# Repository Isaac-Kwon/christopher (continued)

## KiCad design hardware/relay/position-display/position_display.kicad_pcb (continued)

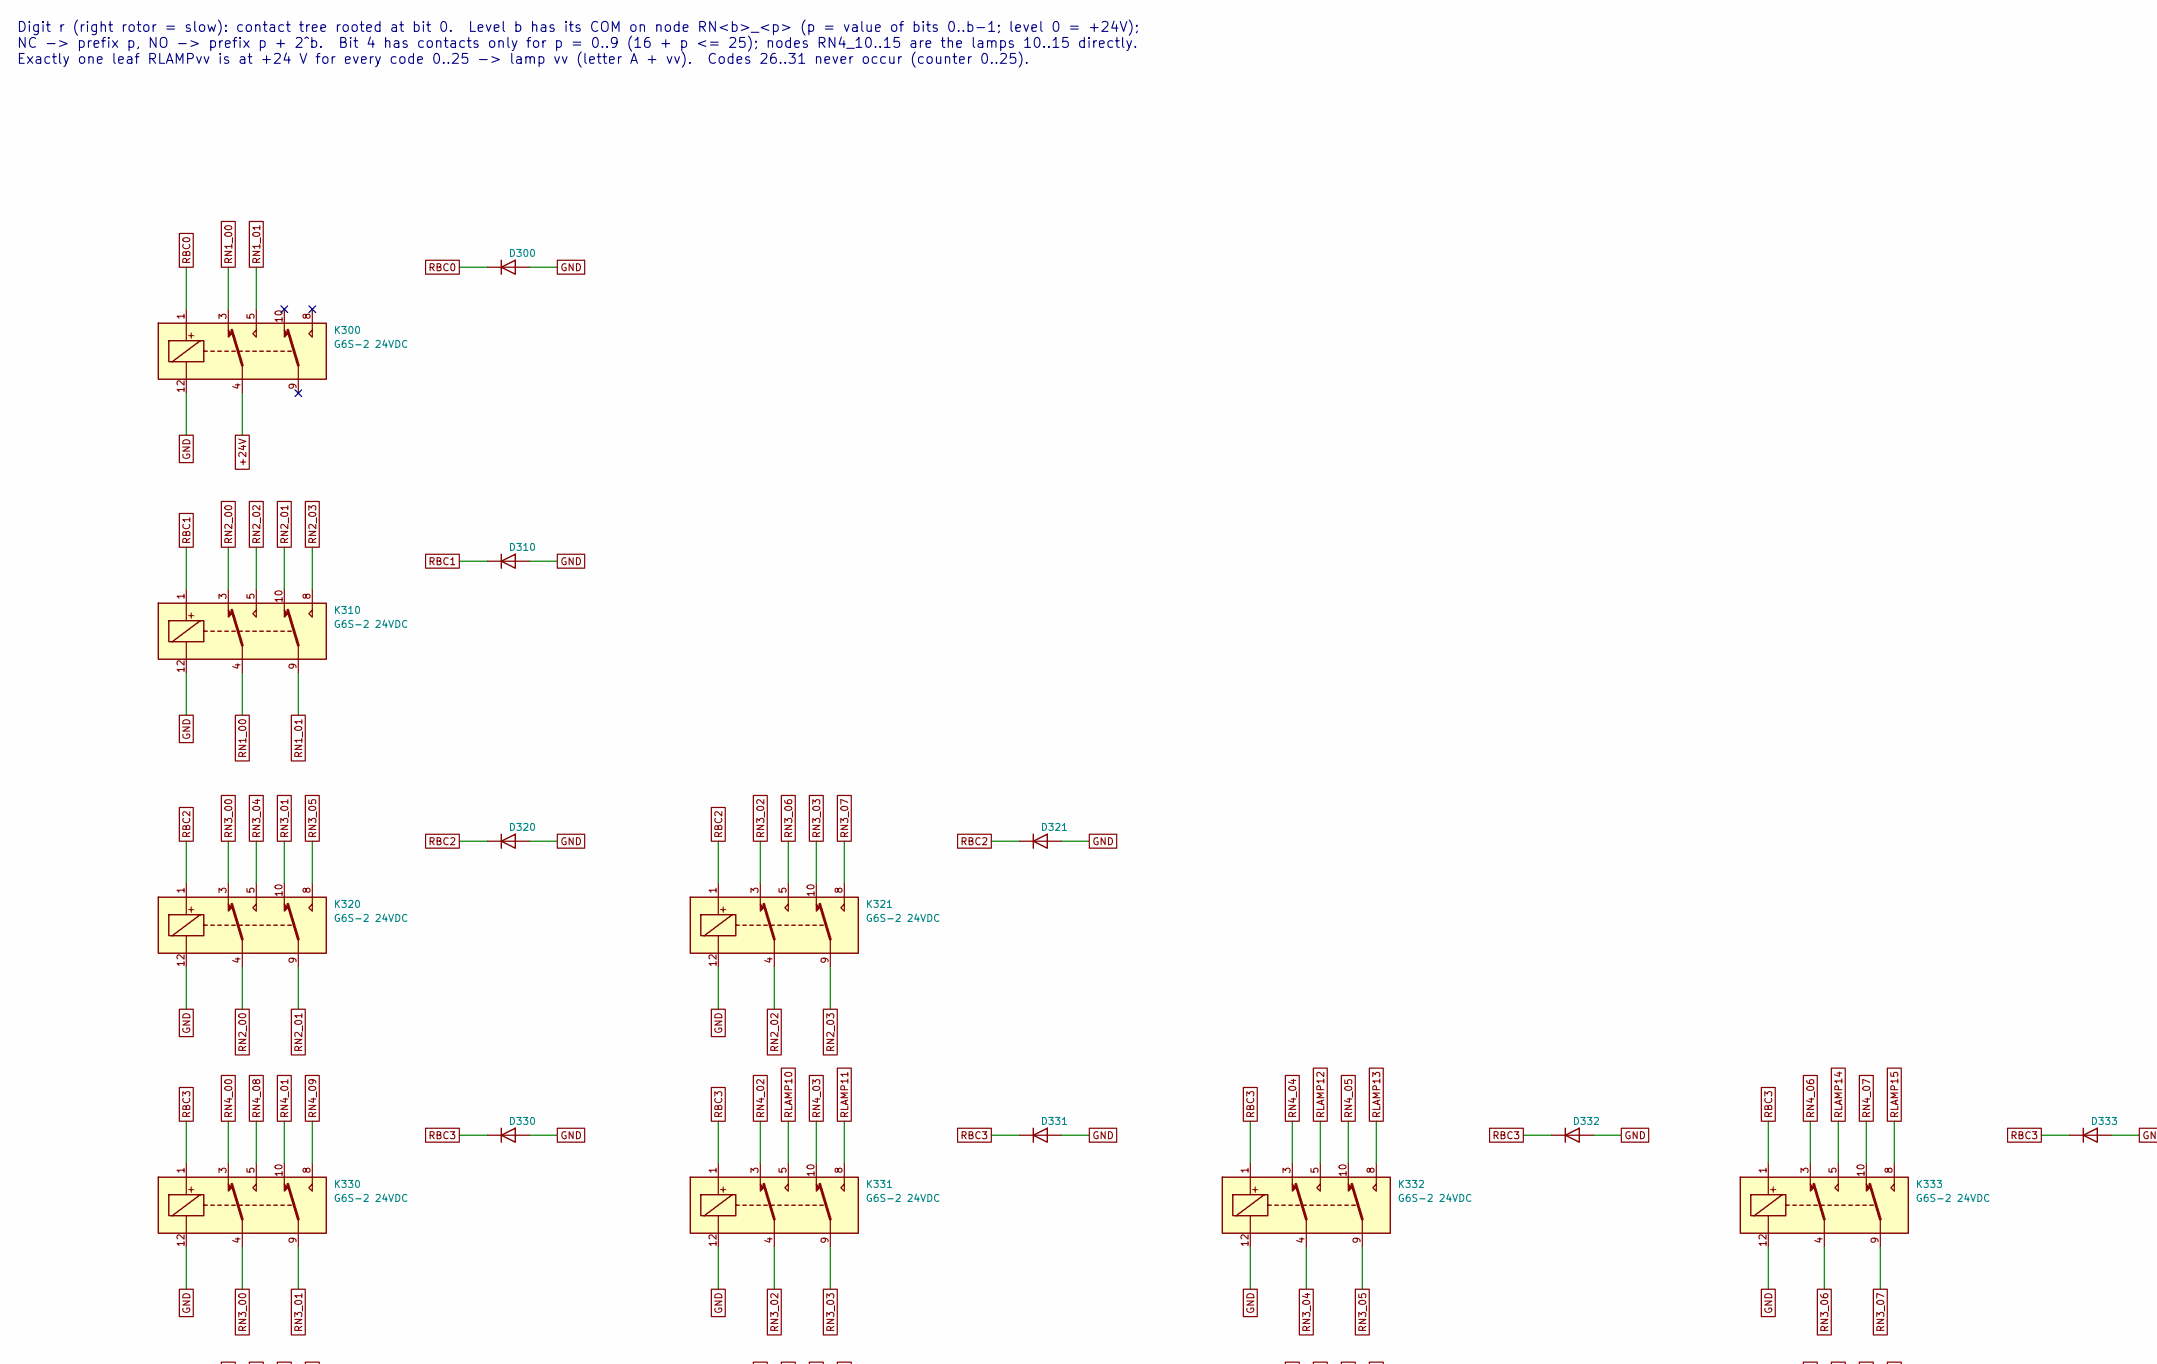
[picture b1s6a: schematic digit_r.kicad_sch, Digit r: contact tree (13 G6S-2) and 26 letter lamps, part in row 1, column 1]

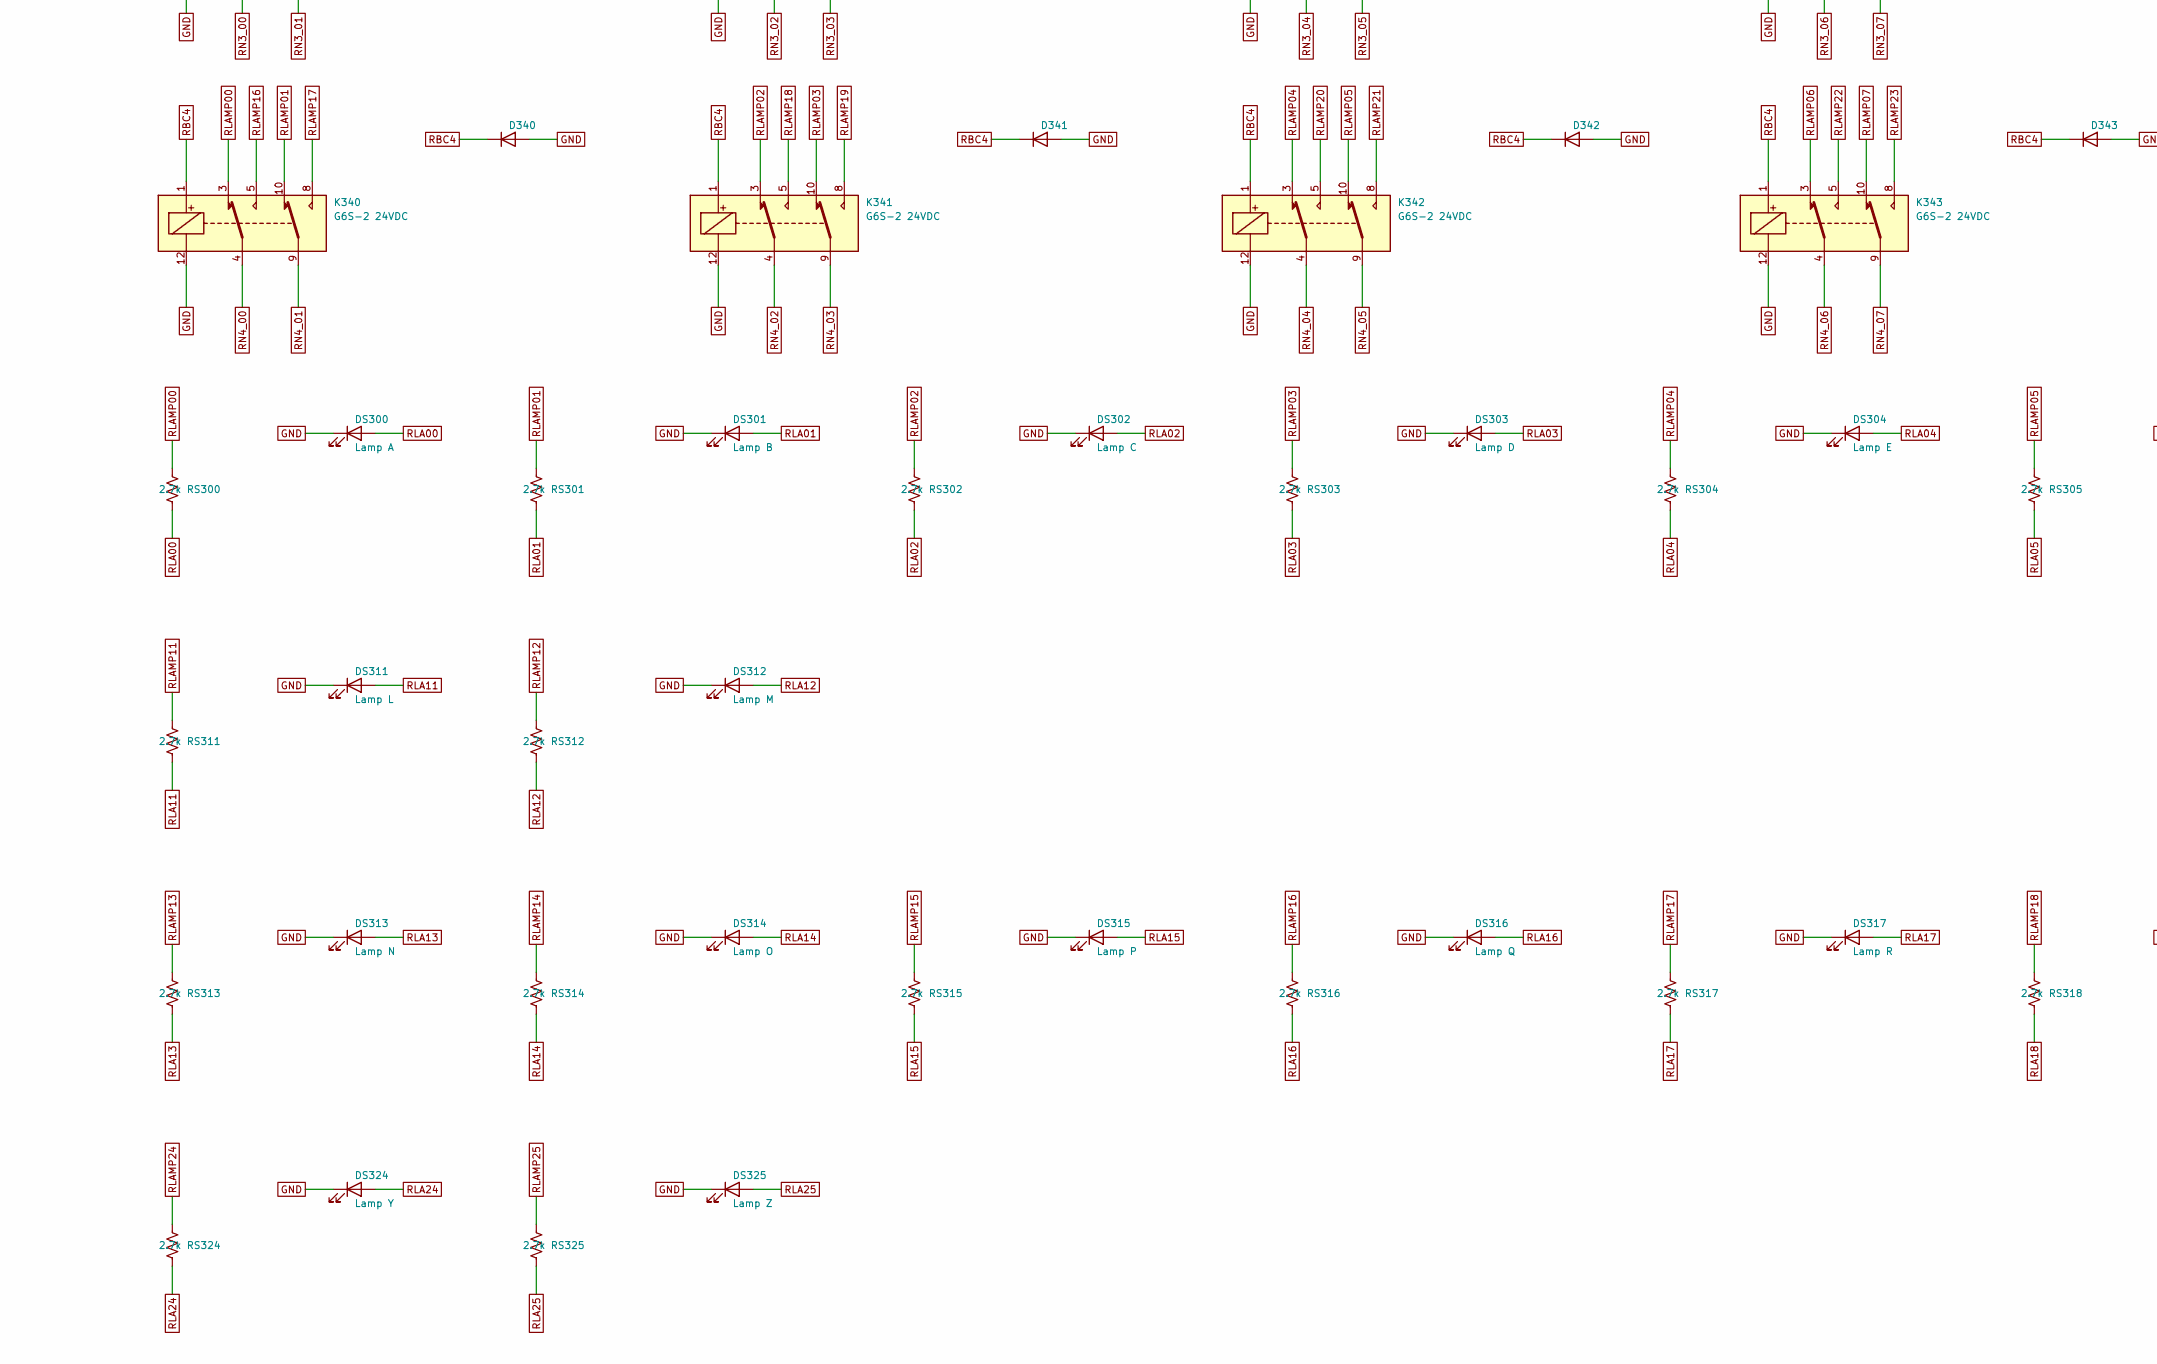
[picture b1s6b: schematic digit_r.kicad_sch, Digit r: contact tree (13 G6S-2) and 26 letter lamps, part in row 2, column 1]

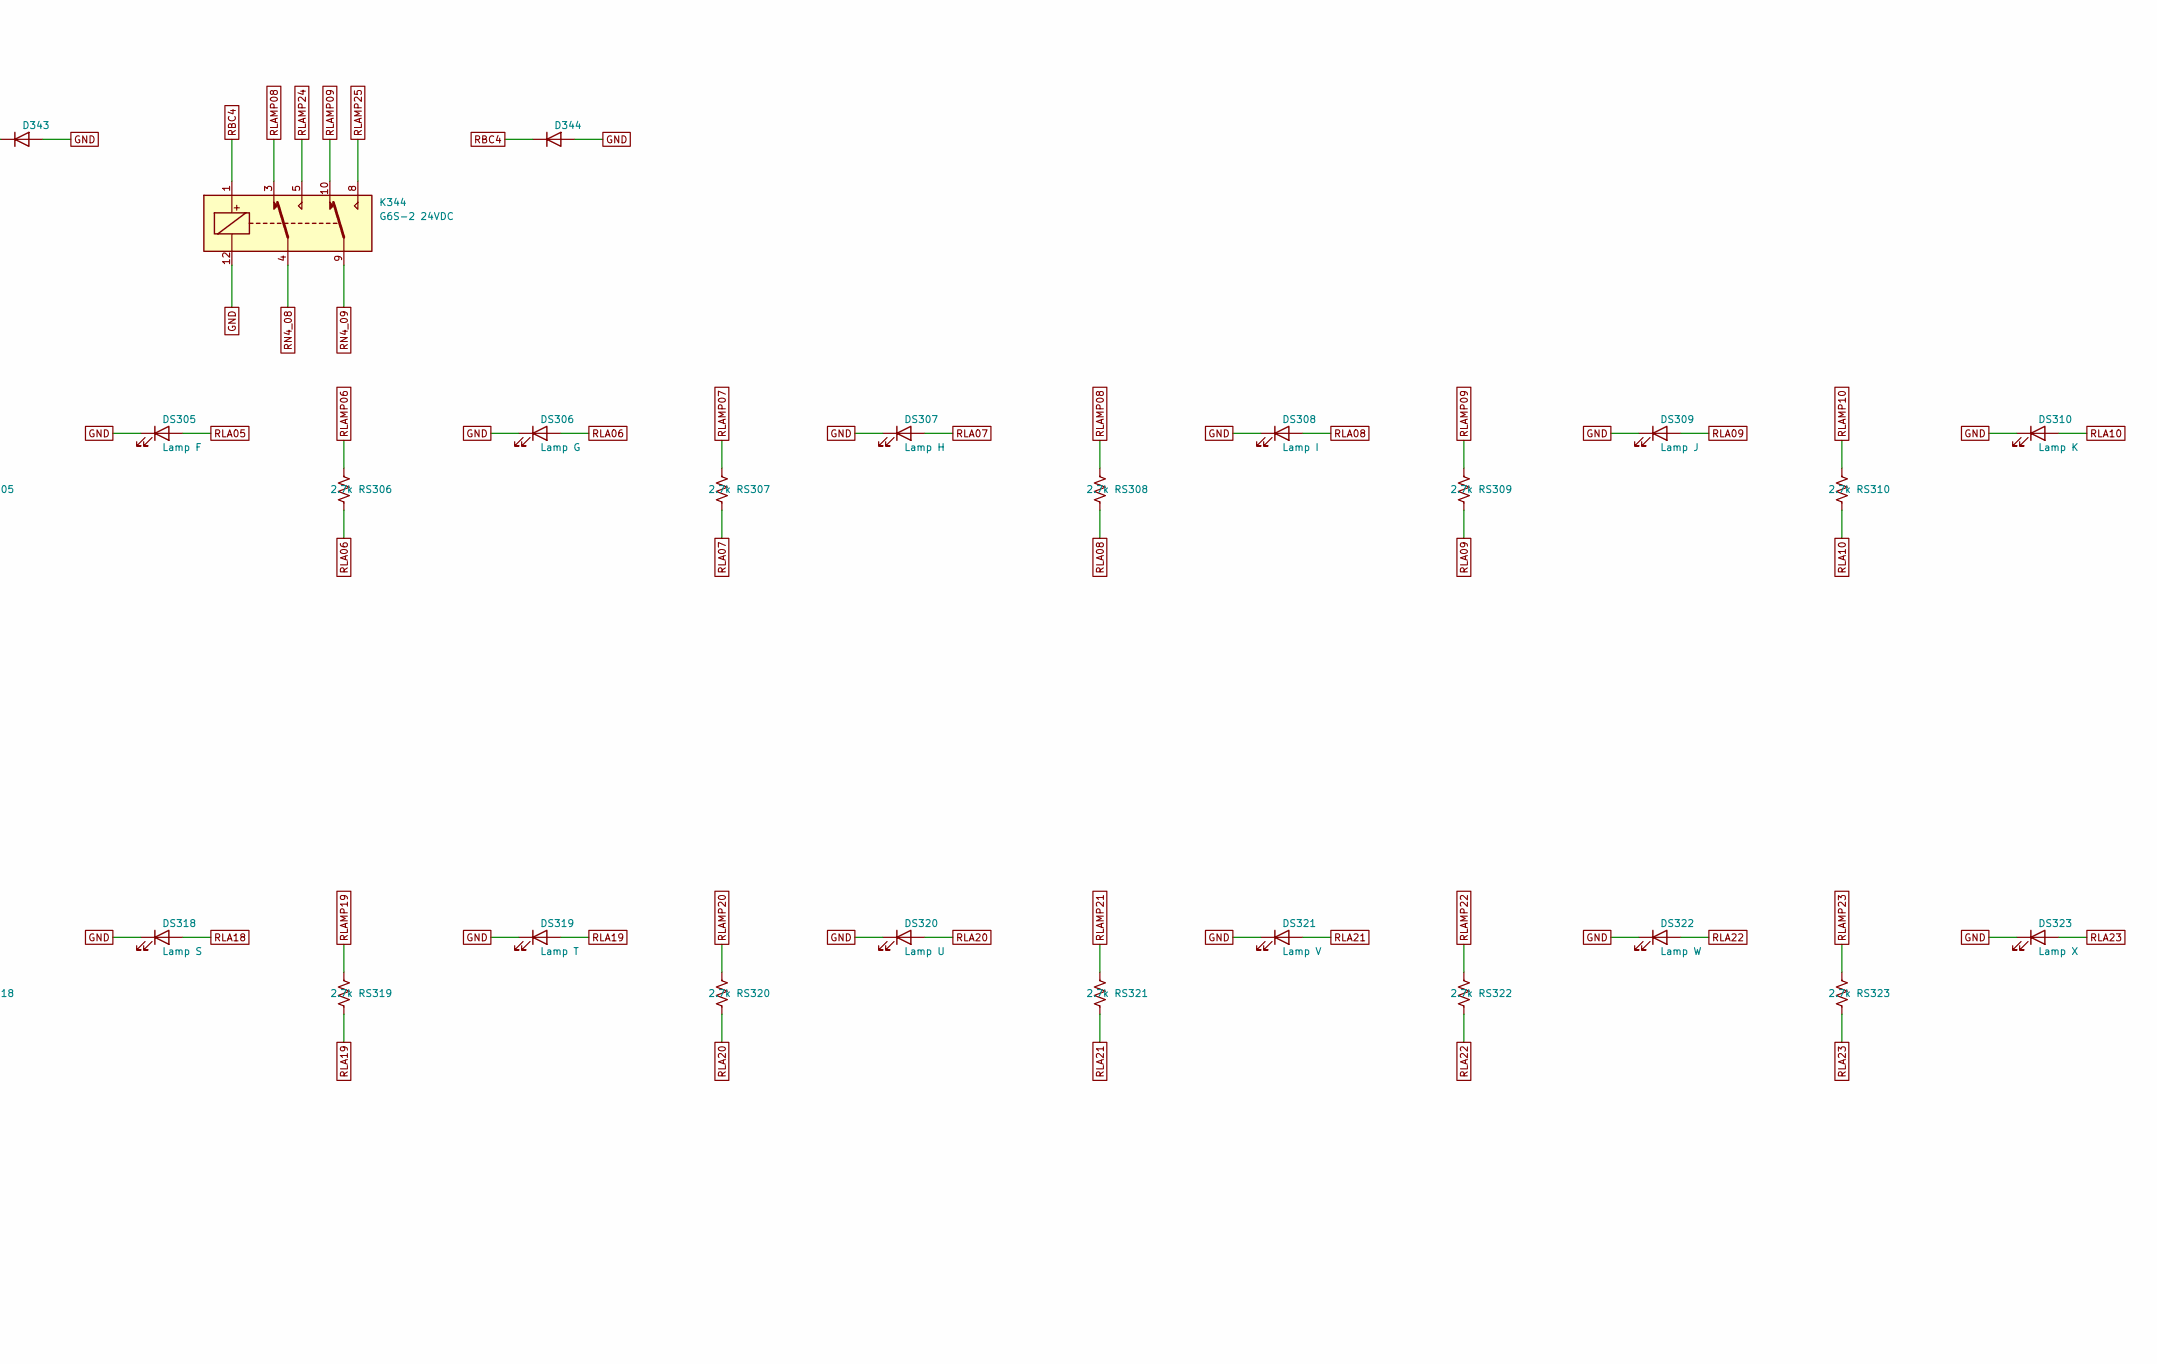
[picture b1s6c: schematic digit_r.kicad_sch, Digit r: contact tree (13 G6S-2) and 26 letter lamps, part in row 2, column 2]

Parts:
D300, D310, D320, D321, D330, D331, D332, D333, D340, D341, D342, D343, D344: 1N4148W; D_SOD-123
DS300: Lamp A; LED_D5.0mm
DS301: Lamp B; LED_D5.0mm
DS302: Lamp C; LED_D5.0mm
DS303: Lamp D; LED_D5.0mm
DS304: Lamp E; LED_D5.0mm
DS305: Lamp F; LED_D5.0mm
DS306: Lamp G; LED_D5.0mm
DS307: Lamp H; LED_D5.0mm
DS308: Lamp I; LED_D5.0mm
DS309: Lamp J; LED_D5.0mm
DS310: Lamp K; LED_D5.0mm
DS311: Lamp L; LED_D5.0mm
DS312: Lamp M; LED_D5.0mm
DS313: Lamp N; LED_D5.0mm
DS314: Lamp O; LED_D5.0mm
DS315: Lamp P; LED_D5.0mm
DS316: Lamp Q; LED_D5.0mm
DS317: Lamp R; LED_D5.0mm
DS318: Lamp S; LED_D5.0mm
DS319: Lamp T; LED_D5.0mm
DS320: Lamp U; LED_D5.0mm
DS321: Lamp V; LED_D5.0mm
DS322: Lamp W; LED_D5.0mm
DS323: Lamp X; LED_D5.0mm
DS324: Lamp Y; LED_D5.0mm
DS325: Lamp Z; LED_D5.0mm
K300, K310, K320, K321, K330, K331, K332, K333, K340, K341, K342, K343, K344: G6S-2 24VDC; Relay_DPDT_Omron_G6S-2
RS300, RS301, RS302, RS303, RS304, RS305, RS306, RS307, RS308, RS309, RS310, RS311, RS312, RS313, RS314, RS315, RS316, RS317, RS318, RS319, RS320, RS321, RS322, RS323, RS324, RS325: 2.7k; R_1206_3216Metric

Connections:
+24V: K300.4; also elsewhere on the board
GND: D300.2 (A), D310.2 (A), D320.2 (A), D321.2 (A), D330.2 (A), D331.2 (A), D332.2 (A), D333.2 (A), D340.2 (A), D341.2 (A), D342.2 (A), D343.2 (A), D344.2 (A), DS300.1 (K), DS301.1 (K), DS302.1 (K), DS303.1 (K), DS304.1 (K), DS305.1 (K), DS306.1 (K), DS307.1 (K), DS308.1 (K), DS309.1 (K), DS310.1 (K), DS311.1 (K), DS312.1 (K), DS313.1 (K), DS314.1 (K), DS315.1 (K), DS316.1 (K), DS317.1 (K), DS318.1 (K), DS319.1 (K), DS320.1 (K), DS321.1 (K), DS322.1 (K), DS323.1 (K), DS324.1 (K), DS325.1 (K), K300.12, K310.12, K320.12, K321.12, K330.12, K331.12, K332.12, K333.12, K340.12, K341.12, K342.12, K343.12, K344.12; also elsewhere on the board
RBC0: D300.1 (K), K300.1; also elsewhere on the board
RBC1: D310.1 (K), K310.1; also elsewhere on the board
RBC2: D320.1 (K), D321.1 (K), K320.1, K321.1; also elsewhere on the board
RBC3: D330.1 (K), D331.1 (K), D332.1 (K), D333.1 (K), K330.1, K331.1, K332.1, K333.1; also elsewhere on the board
RBC4: D340.1 (K), D341.1 (K), D342.1 (K), D343.1 (K), D344.1 (K), K340.1, K341.1, K342.1, K343.1, K344.1; also elsewhere on the board
RLA00: DS300.2 (A), RS300.2
RLA01: DS301.2 (A), RS301.2
RLA02: DS302.2 (A), RS302.2
RLA03: DS303.2 (A), RS303.2
RLA04: DS304.2 (A), RS304.2
RLA05: DS305.2 (A), RS305.2
RLA06: DS306.2 (A), RS306.2
RLA07: DS307.2 (A), RS307.2
RLA08: DS308.2 (A), RS308.2
RLA09: DS309.2 (A), RS309.2
RLA10: DS310.2 (A), RS310.2
RLA11: DS311.2 (A), RS311.2
RLA12: DS312.2 (A), RS312.2
RLA13: DS313.2 (A), RS313.2
RLA14: DS314.2 (A), RS314.2
RLA15: DS315.2 (A), RS315.2
RLA16: DS316.2 (A), RS316.2
RLA17: DS317.2 (A), RS317.2
RLA18: DS318.2 (A), RS318.2
RLA19: DS319.2 (A), RS319.2
RLA20: DS320.2 (A), RS320.2
RLA21: DS321.2 (A), RS321.2
RLA22: DS322.2 (A), RS322.2
RLA23: DS323.2 (A), RS323.2
RLA24: DS324.2 (A), RS324.2
RLA25: DS325.2 (A), RS325.2
RLAMP00: K340.3, RS300.1
RLAMP01: K340.10, RS301.1
RLAMP02: K341.3, RS302.1
RLAMP03: K341.10, RS303.1
RLAMP04: K342.3, RS304.1
RLAMP05: K342.10, RS305.1
RLAMP06: K343.3, RS306.1
RLAMP07: K343.10, RS307.1
RLAMP08: K344.3, RS308.1
RLAMP09: K344.10, RS309.1
RLAMP10: K331.5, RS310.1
RLAMP11: K331.8, RS311.1
RLAMP12: K332.5, RS312.1
RLAMP13: K332.8, RS313.1
RLAMP14: K333.5, RS314.1
RLAMP15: K333.8, RS315.1
RLAMP16: K340.5, RS316.1
RLAMP17: K340.8, RS317.1
RLAMP18: K341.5, RS318.1
RLAMP19: K341.8, RS319.1
RLAMP20: K342.5, RS320.1
RLAMP21: K342.8, RS321.1
RLAMP22: K343.5, RS322.1
RLAMP23: K343.8, RS323.1
RLAMP24: K344.5, RS324.1
RLAMP25: K344.8, RS325.1
RN1_00: K300.3, K310.4
RN1_01: K300.5, K310.9
RN2_00: K310.3, K320.4
RN2_01: K310.10, K320.9
RN2_02: K310.5, K321.4
RN2_03: K310.8, K321.9
RN3_00: K320.3, K330.4
RN3_01: K320.10, K330.9
RN3_02: K321.3, K331.4
RN3_03: K321.10, K331.9
RN3_04: K320.5, K332.4
RN3_05: K320.8, K332.9
RN3_06: K321.5, K333.4
RN3_07: K321.8, K333.9
RN4_00: K330.3, K340.4
RN4_01: K330.10, K340.9
RN4_02: K331.3, K341.4
RN4_03: K331.10, K341.9
RN4_04: K332.3, K342.4
RN4_05: K332.10, K342.9
RN4_06: K333.3, K343.4
RN4_07: K333.10, K343.9
RN4_08: K330.5, K344.4
RN4_09: K330.8, K344.9

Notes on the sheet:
Digit r (right rotor = slow): contact tree rooted at bit 0. Level b has its COM on node RN<b>_<p> (p = value of bits 0..b-1; level 0 = +24V); NC -> prefix p, NO -> prefix p + 2^b. Bit 4 has contacts only for p = 0..9 (16 + p <= 25); nodes RN4_10..15 are the lamps 10..15 directly. Exactly one leaf R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

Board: 4 copper layers, 398 parts (0 on the bottom side), 324 nets, no tracks yet.

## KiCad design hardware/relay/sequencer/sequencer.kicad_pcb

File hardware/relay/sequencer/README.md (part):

# 릴레이식 클럭 순서기 보드 (Phase 3 R 트랙, 회로도 + 기판 배치)

작성일: 2026-11-15 · 상태: **회로도(KiCad 10) 생성·ERC 0건, 넷리스트 스위치 수준 시뮬레이션과 음성 시험 완료, 기판 배치(미배선) 생성·검증 완료, 배선은 사용자가.** 같은 날 `HOME` 끝의 `CLEAR`(0003 4.4절 (나))를 더함. 2026-11-16 다이얼 띠의 **속도 선택(관찰 모드)과 한 걸음 버튼** 입력 J10 `PANEL`을 더함(2.1·3.3절) · 관련: `hardware/relay/offset-dial/README.md` 5절(다이얼 띠 조작 장치), `docs/decisions/0003-interfaces.md`(L1–L9, 4절, 5.2절 제어 커넥터, 8.4절 K7), `docs/decisions/0001-test-register-timing.md`, `hardware/relay/counter-board/README.md`(2.5절 CK/NCK·HOME, 4절 타이밍, 8절), `hardware/relay/concept.md` 6절, `hardware/relay/layout.md` 3.5·3.7절(자리 250 × 228 × 40, 대기), `hardware/common/power-unit.md`(F38, `+24V_SW`)

**표기.** **(계산)** = 이 문서의 산술, **(추정)** = 실측 전 값, **(미확인)** = 데이터시트로 확인하지 못한 것.

## 1. 무엇인가

릴레이식 뱅크의 **위치 순서기**다. 한 위치마다 `CK`/`NCK`(두 상, 단일 전환 접점), `STROBE`·`JUDGE`·`CLEAR`를 0003 L1–L9의 폭과 간격으로 내고, `RUN`·`STOP_LATCH`·`HOME`을 받아 정지·재출발·`HOME`(프리셋)·`END`·대기를 처리한다. 다이얼 띠의 **속도 선택**(빠름 63 ms / 관찰 270 ms)과 **한 걸음 버튼**(누를 때마다 위치 주기 하나)을 J10으로 받는다. 계수기 공통 보드의 `POS`(l, m, r)를 제어 커넥터 7–21번으로 중계하고, 안전 고리(`ESTOP`, `ILOCK`)의 뱅크 쪽 자리를 준다.

| 항목 | 값 |
|---|---|
| 릴레이 | **G6S-2 50개**(기능 릴레이 33 + 접점을 늘리는 쌍둥이 17). 그 가운데 6개(`KOBS`, `KSP`, `KSA`(+b), `KSC`(+b))가 속도 선택·한 걸음 |
| 능동 부품 | LMC555 1, 74HC4017 1, TBD62783A 2, TSR 1-2450(5 V) 1 |
| 다이오드류 | 다이오드 72, 쇼트키 8, 제너 16(+ 게이트 제너 1), TVS 1, P채널 MOSFET 1 |
| 그 밖 | 자동 복귀 퓨즈 27, 저항 65, 커패시터 12, LED 33, 트리머 1, 납땜 점퍼 3 |
| 커넥터 | D-sub 37 수 1(제어), D-sub 25 수 2(`POS` 입력, `UNIT_BUS` 탭), D-sub 9 수 2(`CLOCK` A/B), 나사 단자 4극 3 + 2극 2 |
| 부품 합계 | 309개(장착 구멍 4 포함) |
| 기판 | 250 × 228 mm 4층(시프터·계수기와 같은 카드 규격), 높이 40 mm 이내 **(계산)**: 가장 높은 부품 100 µF 전해 12 mm, 릴레이 10 mm |

### 1.1 원리: 릴레이가 정한다, 시간 기준만 전자식

설계 원칙("릴레이가 판정한다, 전자 장치는 시간만 알린다")에 맞춰 **순서·조건·잠금은 전부 릴레이 접점**이다: 위치 한 주기의 단계 선택, `RUN`을 본 뒤의 `CK` 결정(`KCKH`), 정지 뒤의 "나아가기 먼저"(`KADV`), `HOME` 순서(`KHL`), 프리셋 중의 `LOAD`·`NCK` 겹침, `END` 판정(`KR25`·`KEND`), 대기(`KSB`), 비상 정지 때의 전부 놓기. 모든 출력은 릴레이 접점이 +24 V를 잇는 방식이다.

**전자식인 것은 시간 기준 하나**다: LMC555(발진기) + 74HC4017(링 계수기), 곧 "6.3 ms마다 다음 단계"라는 박자다. 이것은 기어식에서 광센서와 슬롯 원판이 하는 일("언제")과 같고, 정지·진행 여부는 결정하지 않는다. 릴레이 시간 기준을 쓰지 않은 이유(요약):

1. 0003의 폭·간격은 모두 하한이다. 하한을 **보증**하려면 타이밍 편차가 릴레이 동작 편차(2.5–5 ms)보다 작아야 한다. RC로 지연시키는 릴레이는 동작 전압이 정격의 일정 비율 **이상**이라는 값(최대 80% **(미확인)**)만 알려져 있어 지연의 하한을 보증할 수 없다(동작 전압 50–80%면 같은 RC의 지연이 2배 이상 흩어진다 (계산)).
2. 릴레이 사슬로 박자를 만들면 단계마다 편차가 쌓여(릴레이 하나 최대 ±1.25 ms 편차, 사슬 길이만큼) 위치 주기가 70–80 ms가 된다.
3. 전자식 클럭을 기본으로 하고 릴레이 발진기는 전시 요소로 선택할 수 있게 한다는 `concept.md` 6절의 방침과 같다. 발진기를 릴레이로 바꿀 자리는 U1 하나다(10 kΩ·22 nF의 RC가 박자를 정한다).

**속도 선택도 박자만 바꾼다.** 관찰 모드는 555의 R2에 680 kΩ을 직렬로 넣어(평소에는 릴레이 접점 두 개가 이 저항을 단락한다) 틱을 27 ms로 늘린다(2.1절). 어느 단계가 언제 나오는지, 주기를 시작·완료하는지는 그대로 릴레이 접점이 정한다. 한 걸음 버튼도 마찬가지로 "주기 하나를 시작해도 된다"를 릴레이 래치로 만들 뿐이다(3.3절).

링 계수기의 출력은 **창**(다이오드 OR)이 되어 TBD62783A(24 V 고측 구동기)의 입력이 되고, 그 출력이 출력 릴레이의 코일을 먹인다. 창과 구동기 사이에는 릴레이 접점이 직렬로 들어간다(`KENW`, `KENK`, `KCKH`, `KHL` …): 접점이 닫혀 있어야만 창이 코일에 닿는다.

## 2. 위치 한 주기의 시각표

링 상태 Q0–Q9(한 틱 T = 6.3 ms, 한 주기 10틱 = **63 ms**, 트리머로 T 4.7–7.8 ms)와 릴레이 출력 **(커넥터 면, 계산: 시뮬레이션이 확인)**:

| 링 상태 | 창 | 구동되는 릴레이 | 하는 일 |
|---|---|---|---|
| Q0–Q1 | WS | `KS` (게이트 `KENW`) | `STROBE` |
| Q3–Q4 | WJ | `KJ` (게이트 `KENW`) | `JUDGE` |
| Q6 | — | `KCKH` 표본(`RUN`이 높을 때, 또는 한 걸음 주기에 `STOP_LATCH`가 낮을 때) | `CK`를 낼지 결정, 닫히면 Q6–Q8(WC)로 스스로 유지 |
| Q6–Q8 | WC | `KC` (게이트 `KENK`) | `CLEAR` |
| Q7–Q8 | WK | `KCKA`·`KCKB` (게이트 `KENK`, `KCKH`) | `CK` (결정 `KCKH`가 닫혔으면) 또는 나아가기 보류 `KADV` 세트(열렸으면) |
| Q9 | — | `KST`(주차) | 링이 선다(`KGO`가 없을 때), `STOPPED` |

| 규칙 (0003 3.3절) | 요구 | 시뮬레이션 최소값(릴레이 시간 최악·최선·무작위, 링 ±3%; 속도 전환·한 걸음 시나리오 포함) | 여유 |
|---|---|---|---|
| L1 `STROBE` 폭 | ≥ 7.5 ms | 8.23 | 0.73 |
| L2 `JUDGE` 오름 − `STROBE` 오름 | ≥ 11.5 | 15.66 | 4.2 |
| L3 `JUDGE` 폭 | ≥ 7.5 | 8.23 | 0.73 |
| L4 `CLEAR` 오름 − `JUDGE` 내림 | ≥ 1.5 | 4.86 | 3.4 |
| L5 `CLEAR` 폭 | ≥ 12.5 | 14.40 | 1.9 |
| L6 다음 `STROBE` 오름 − `CLEAR` 내림 | ≥ 1.5 | 4.85 | 3.4 |
| L9 `CK` 오름 → 다음 `STROBE` 오름(시프터 안정 13) | ≥ 13 | 15.69 | 2.7 |
| `CK` 폭(계수기가 요구하는 5 ms) | ≥ 5 | 8.23 | 3.2 |
| `HOME` 끝의 `CLEAR` 폭 (L5, 3.2절) | ≥ 12.5 | 14.54 | 2.0 |
| 첫 `STROBE` 오름 − `HOME` 끝 `CLEAR` 내림 (L6, `HOME` 중에 시작 스위치를 켠 경우) | ≥ 1.5 | 20.68 | 19 |

- **주기는 63 ms, 초당 15.9 위치**(전체 17,576 위치 약 18.5분, 90번 정지를 넣은 전체 시뮬레이션은 18.8분)다. `concept.md` 6절의 35 ms(10.3분)는 **출력 쪽 타이밍 편차가 0일 때** 성립하는 값이다. 릴레이 접점이 출력이면 `STROBE` 폭만 해도 구동 폭 + (복귀 − 동작) = 구동 폭 − 3.5…4.1 ms로 줄어(동작 2.5–5, 복귀 1.5–4, 접점 전환 0.2–0.6 **(추정)**) 구동 창이 11.6 ms 이상이어야 한다. 그래서 최소 틱 T는 5.8 ms이고(`STROBE` 폭 기준), 기본을 6.3 ms로 잡아 0.7 ms의 여유를 둔다. 접점 타이밍을 실측(R.1)해 보정하면 T를 줄일 수 있다(트리머 RV1). 이 값은 **0003이 정한 35 ms를 넘는 부분을 이 설계가 책임지는 것이다**(11절 1번).
- `CK`는 `CLEAR`의 오름과 같은 위상(Q6)에서 정하고 Q7에서 낸다. 오름이 `CLEAR`보다 3.3 ms 이상 뒤다(L9의 앞쪽 조건).
- 정지 판정은 `JUDGE` 접점(레지스터 안)이 정하고, 순서기는 `RUN`이 내려간 것을 `KR` → `KCKH`로 본다. 레지스터의 정지로 `RUN`이 내려가면 최악 조합에서도 `KR`이 Q6 시작 뒤 0.6 ms 안에 열려, `KCKH`의 표본 구동(릴레이가 동작하려면 2.5 ms 이상 필요)이 취소된다 (계산, 시뮬레이션이 최악 조합으로 확인).

### 2.1 관찰 모드 (속도 선택, J10 2번)

관찰 모드는 **같은 링, 같은 창, 더 긴 틱**이다. 555의 R2에 680 kΩ을 직렬로 넣어 T = 0.693 (R1 + 2 (R2 + RV1 + 680 k)) C = **27.0 ms**(트리머를 6.3 ms에 맞춘 상태), 한 주기 10틱 = **270 ms, 초당 3.7 위치**(구간 676 위치 3.0분, 전체 79분)다. 커패시터 ±3%에서 262–278 ms, 트리머를 끝까지 돌려도 255–285 ms로 늘 초당 4 위치 이하다 (계산). 평소에는 `KOBS`의 NC와 `KSCb`의 NC가 직렬로 이 저항을 단락한다. 선택 스위치를 관찰에 두면(`KOBS`가 붙음) 또는 한 걸음 주기 중이면(`KSCb`가 붙음, 3.3절) 단락이 열린다.

| 링 상태 | 하는 일 | 빠름 (T = 6.3) | 관찰 (T = 27.0) |
|---|---|---:|---:|
| Q0–Q1 | `STROBE` | 0–12.6 | 0–54 |
| Q3–Q4 | `JUDGE` | 18.9–31.5 | 81–135 |
| Q6 | `CK` 결정 | 37.8 | 162 |
| Q6–Q8 | `CLEAR` | 37.8–56.7 | 162–243 |
| Q7–Q8 | `CK` | 44.1–56.7 | 189–243 |
| Q9 | 주차 또는 다음 주기 | 56.7–63 | 243–270 |

| 관찰 모드 (커넥터 면) | 요구 | 시뮬레이션 최소값 |
|---|---|---:|
| L1 `STROBE` 폭 / L3 `JUDGE` 폭 | ≥ 7.5 | 48.9 / 48.8 |
| L2 `JUDGE` 오름 − `STROBE` 오름 | ≥ 11.5 | 76.8 |
| L4 `CLEAR` 오름 − `JUDGE` 내림 / L6 다음 `STROBE` − `CLEAR` 내림 | ≥ 1.5 | 25.2 / 25.2 |
| L5 `CLEAR` 폭 (`HOME` 끝의 `CLEAR` 포함) | ≥ 12.5 | 75.4 (75.3) |
| L9 `CK` 오름 → 다음 `STROBE` | ≥ 13 | 76.5 |
| 위치 주기(`STROBE` → 다음 `STROBE`) | ≥ 250 (초당 4 이하) | 261.7 |

**왜 저항을 바꾸는가 (커패시터나 분주기가 아니라).** 0003의 규칙은 모두 하한이므로 틱이 길어지는 것은 괜찮고, 짧아지는 것만 위험하다. 바꾸는 순간은 운전 중 아무 때나다(관람객이 돌린다).

- **저항을 바꾸면** 커패시터 전압은 이어지고 충방전의 빠르기만 바뀐다. 저항이 빠른 모드의 값 이상인 동안 전압은 빠른 모드보다 빨리 움직일 수 없으므로, **어떤 틱도(바꾸는 순간이 걸린 틱, 접점이 튀는 동안의 틱도) 빠른 틱보다 짧지 않다.** 링 상태의 길이가 모두 빠른 틱 이상이면 L1–L9는 빠른 모드에서 성립한 그대로 성립한다(각 규칙이 틱 길이의 합이므로). 주기는 링이 한 번 Q9를 떠나면 Q9까지 반드시 도므로 끊기지 않고, `CK`는 주기마다 Q7–Q8 한 번뿐이다(L7, `CK` 겹침 없음).
- **커패시터를 더하면** 충전된 C와 빈 C가 전하를 나눠 전압이 순간 떨어지고, 방전 중이었다면 바로 1/3 Vcc 아래로 내려가 출력이 올라간다: 그 틱이 반 틱(약 3 ms)으로 잘려 `STROBE`·`JUDGE` 폭(L1, L3)을 어길 수 있다.
- **분주기**(4017 하나 더)로 클럭을 고르면 두 클럭을 비동기로 바꾸는 순간 틱이 임의로 짧아진다. 동기화하려면 전자 부품이 더 늘어 "전자식은 시간 기준 하나"의 원칙에서 멀어진다.

시뮬레이션은 555를 넷리스트의 RC로 모사하고(그 순간 닫힌 접점으로 이어진 저항의 합, 바뀌면 전압을 이어서 계산), 운전 중 선택 스위치를 무작위 시각에 36번씩 뒤집어도 가장 짧은 555 주기가 빠른 틱의 0.997배(흔들림 ±0.3% 안)였다(6절).

관찰 모드에서 길어지는 것: `HOME`의 `LOAD`(Q3–Q6)가 25 ms에서 약 108 ms로, `STROBE` 중 시험 전압이 54 ms 걸린다. 앞의 것은 버스마다의 `LOAD` 퓨즈(유지 0.1 A)에 프리셋 전류 약 0.4 A가 그만큼 흐른다는 뜻이다(11절 4번).

## 3. 회로 구성

KiCad 계층 회로도(`sequencer.kicad_sch` + 일곱 장, 넷 이름은 전부 전역). 재생성은 `gen_sequencer.py`, 부품·넷의 정의는 `seqdesign.py`에 한 번만 있다.

| 시트 | 내용 |
|---|---|
| `POWER` | `+24V_SW` 입력 J1 → PTC 3 A → 직렬 P채널 MOSFET → TVS 33 V + 470 µF → TSR 1-2450(5 V). `CHASSIS`(장착 구멍 4 + D-sub 껍데기)와 `CHASSIS`–0 V 1 MΩ ∥ 10 nF |
| `TIMEBASE` | LMC555 비안정(R1 10 kΩ, R2 150 kΩ + 트리머 100 kΩ, **관찰 저항 680 kΩ**(`KOBS`·`KSCb`의 NC 접점이 평소에 단락), C 22 nF C0G) + 74HC4017 링 + 링 표시 LED 10 + 창 다이오드 OR(`WS`, `WJ`, `WC`, `WK`, `HKON`, `HLD`) |
| `DRIVERS` | TBD62783A 둘: 1번은 `STROBE`·`JUDGE`·`CLEAR`·`CK`·`KEN`·`LOAD`·완료·나아가기 보류 릴레이, 2번은 `KST`(주차), `KCKH`, 한 걸음 주기 `KSC`(3번 채널). 입력마다 47 kΩ 풀다운 |
| `INPUTS` | 입력 추종 릴레이: `RUN`(`KR`), `STOP_LATCH`(`KSL`), `HOME`(`KHM`), `POS10/13/14`(`KP0/3/4`), 속도 선택(`KOBS`), 한 걸음(`KSP`), 서모스탯(`KHT`). 핀 → 직렬 쇼트키 → 코일, 코일 쪽 클램프(다이오드 + 제너 30 V, `KOBS`·`KSP`는 다이오드만), 핀 쪽 22 kΩ 풀다운 + LED (0003 2.2절) |
| `LOGIC` | 상태·게이트 릴레이(아래 표), 한 걸음 래치(`KSA`, `KSC`) |
| `OUTPUTS` | 출력 릴레이와 출력 퓨즈 |
| `CONNECTORS` | J2–J10 |

### 3.1 릴레이의 역할

| 릴레이 | 역할 |
|---|---|
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
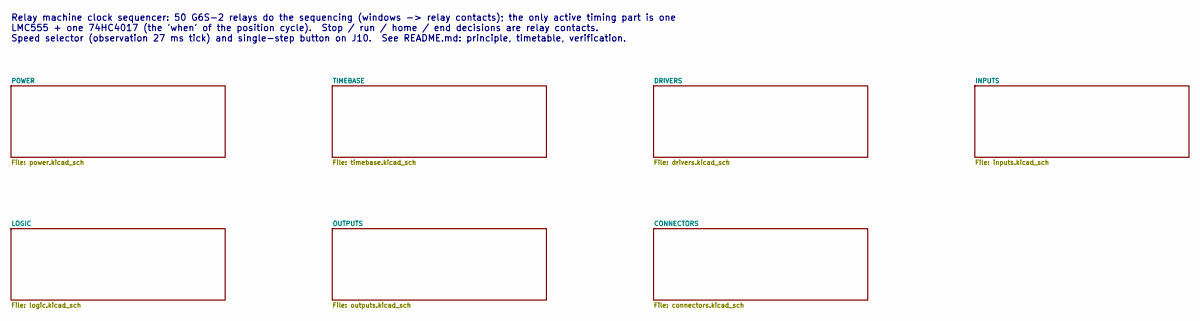
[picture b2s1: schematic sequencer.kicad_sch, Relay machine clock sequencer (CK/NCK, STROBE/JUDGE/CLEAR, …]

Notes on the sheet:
Relay machine clock sequencer: 50 G6S-2 relays do the sequencing (windows -> relay contacts); the only active timing part is one LMC555 + one 74HC4017 (the 'when' of the position cycle). Stop / run / home / end decisions are relay contacts. Speed selector (observation 27 ms tick) and single-step bu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

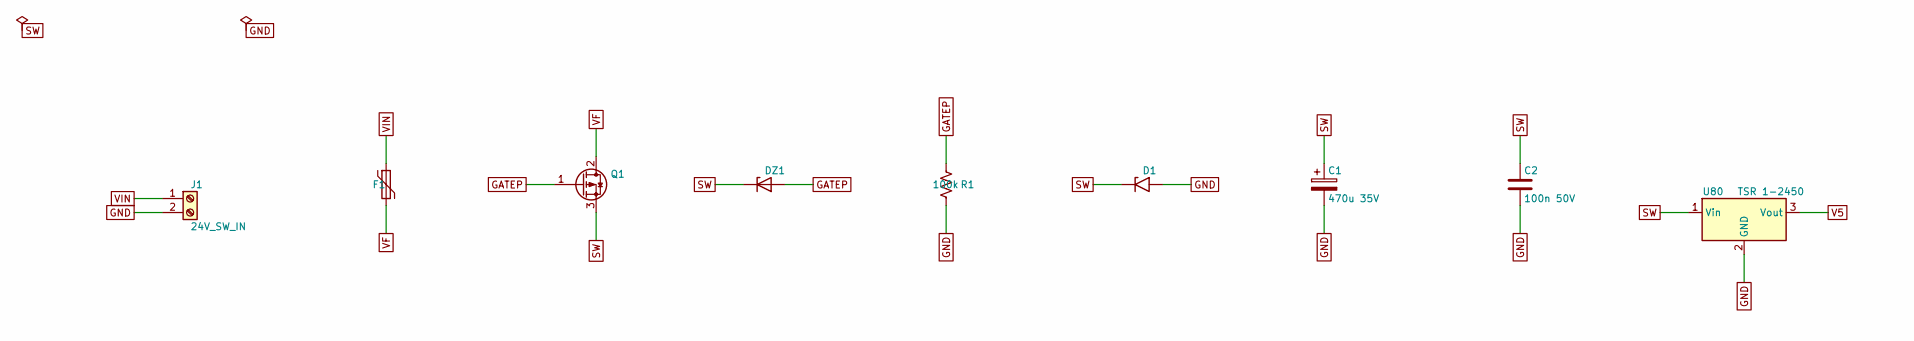
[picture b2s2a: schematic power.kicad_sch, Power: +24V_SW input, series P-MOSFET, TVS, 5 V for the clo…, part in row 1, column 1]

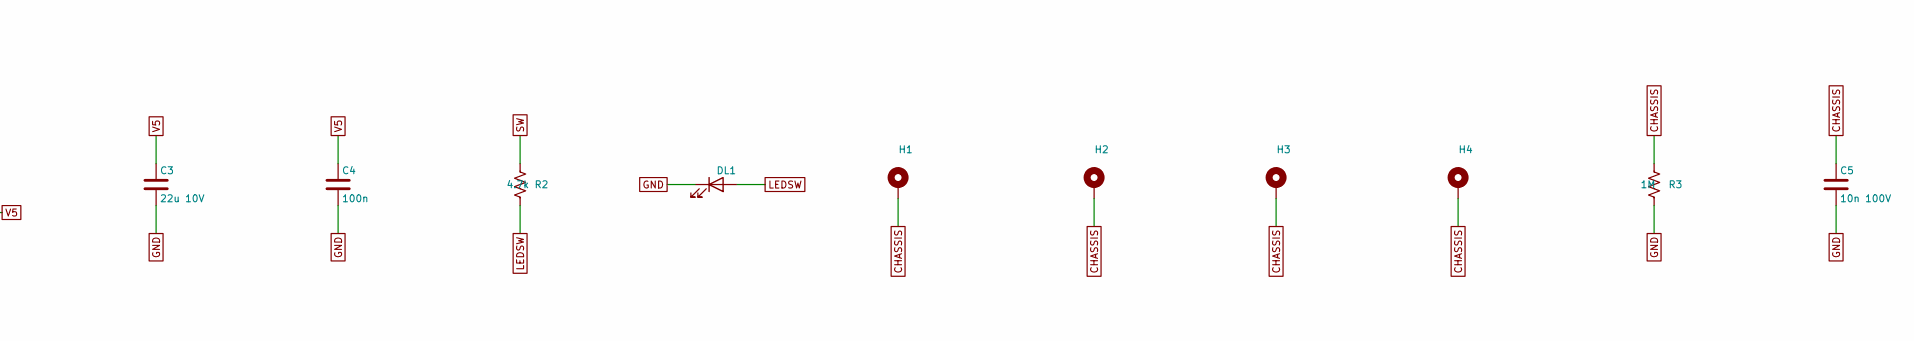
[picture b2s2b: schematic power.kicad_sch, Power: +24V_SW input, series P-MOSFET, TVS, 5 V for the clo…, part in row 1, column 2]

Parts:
C1: 470u 35V; CP_Radial_D10.0mm_P5.00mm
C2: 100n 50V; C_0805_2012Metric
C3: 22u 10V; C_1206_3216Metric
C4: 100n; C_0603_1608Metric
C5: 10n 100V; C_0603_1608Metric
D1: SMAJ33A; D_SMA
DL1: +24V_SW; LED_0603_1608Metric
DZ1: 12V; D_SOD-123
F1: PTC 3A hold; Fuse_2920_7451Metric
H1, H2, H3, H4: MountingHole_Pad; MountingHole_3.2mm_M3_Pad
J1: 24V_SW_IN; TerminalBlock_Phoenix_MKDS-1,5-2-5.08_1x02_P5.08mm_Horizont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
Q1: P-MOSFET (reverse polarity); SOT-223-3_TabPin2
R1: 100k; R_0603_1608Metric
R2: 4.7k; R_0603_1608Metric
R3: 1M; R_0603_1608Metric
U80: TSR 1-2450; Converter_DCDC_TRACO_TSR-1_THT

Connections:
CHASSIS: C5.1, H1.1, H2.1, H3.1, H4.1, R3.1; also elsewhere on the board
GATEP: DZ1.2 (A), Q1.1 (G), R1.1
GND: C1.2, C2.2, C3.2, C4.2, C5.2, D1.2 (A2), DL1.1 (K), J1.2, R1.2, R3.2, U80.2 (GND); also elsewhere on the board
LEDSW: DL1.2 (A), R2.2
SW: C1.1, C2.1, D1.1 (A1), DZ1.1 (K), Q1.3 (S), R2.1, U80.1 (Vin); also elsewhere on the board
V5: C3.1, C4.1, U80.3 (Vout); also elsewhere on the board
VF: F1.2, Q1.2 (D)
VIN: F1.1, J1.1

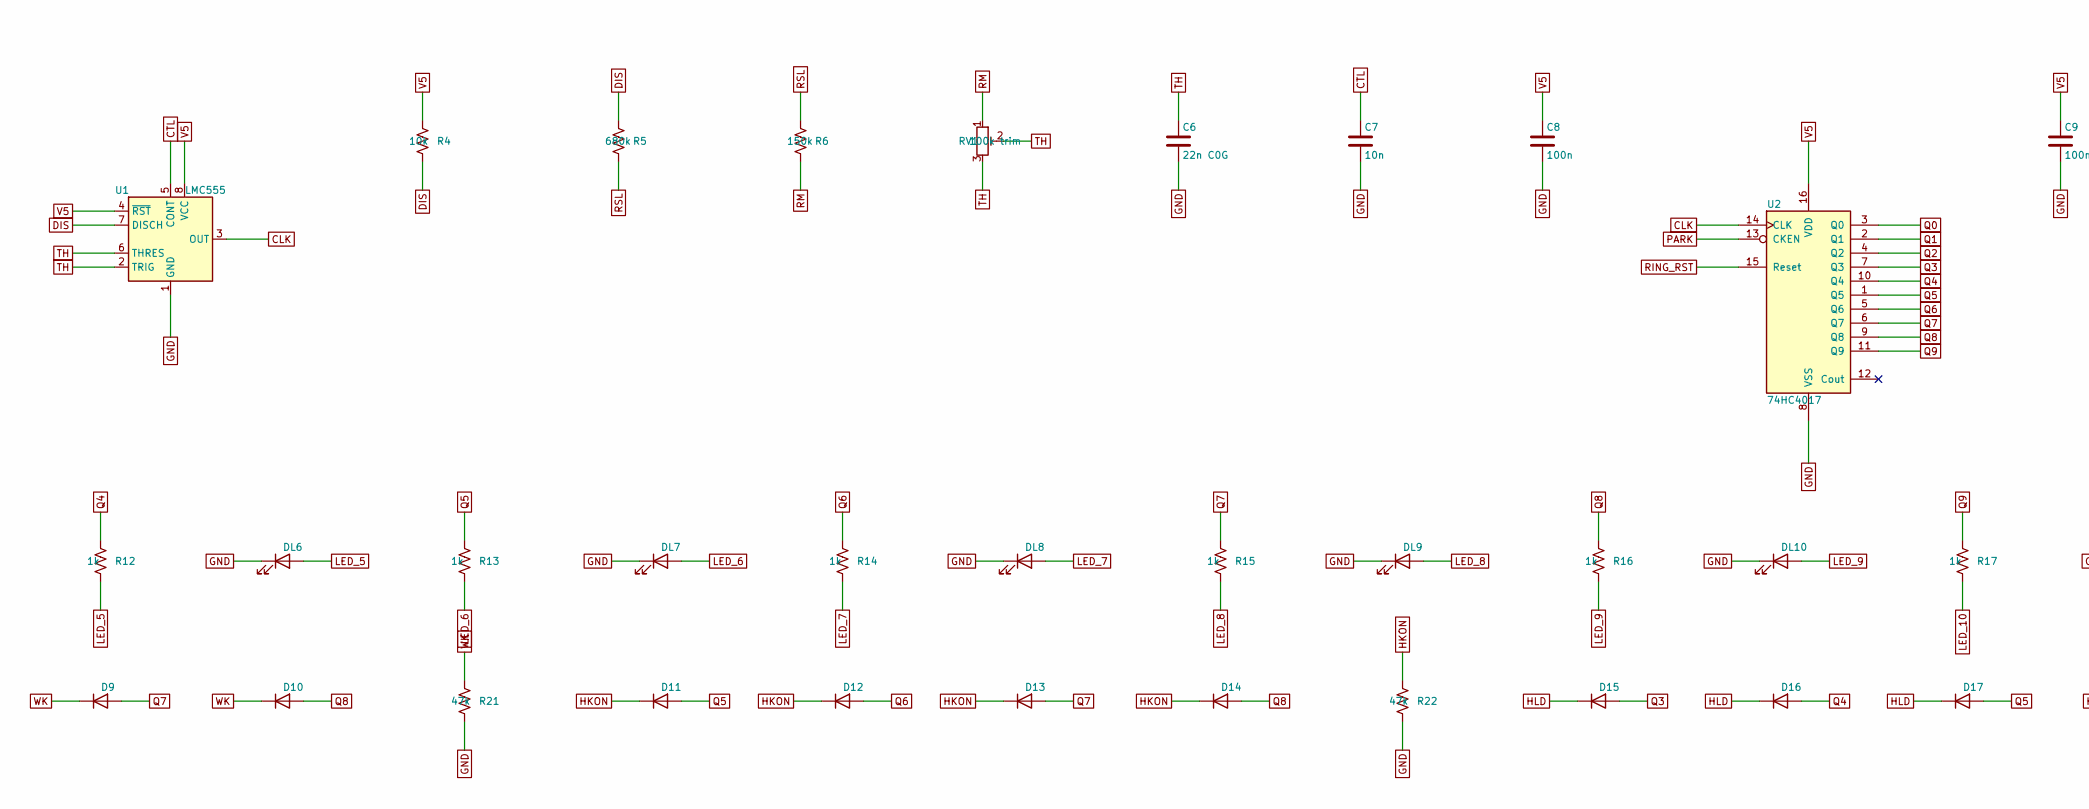
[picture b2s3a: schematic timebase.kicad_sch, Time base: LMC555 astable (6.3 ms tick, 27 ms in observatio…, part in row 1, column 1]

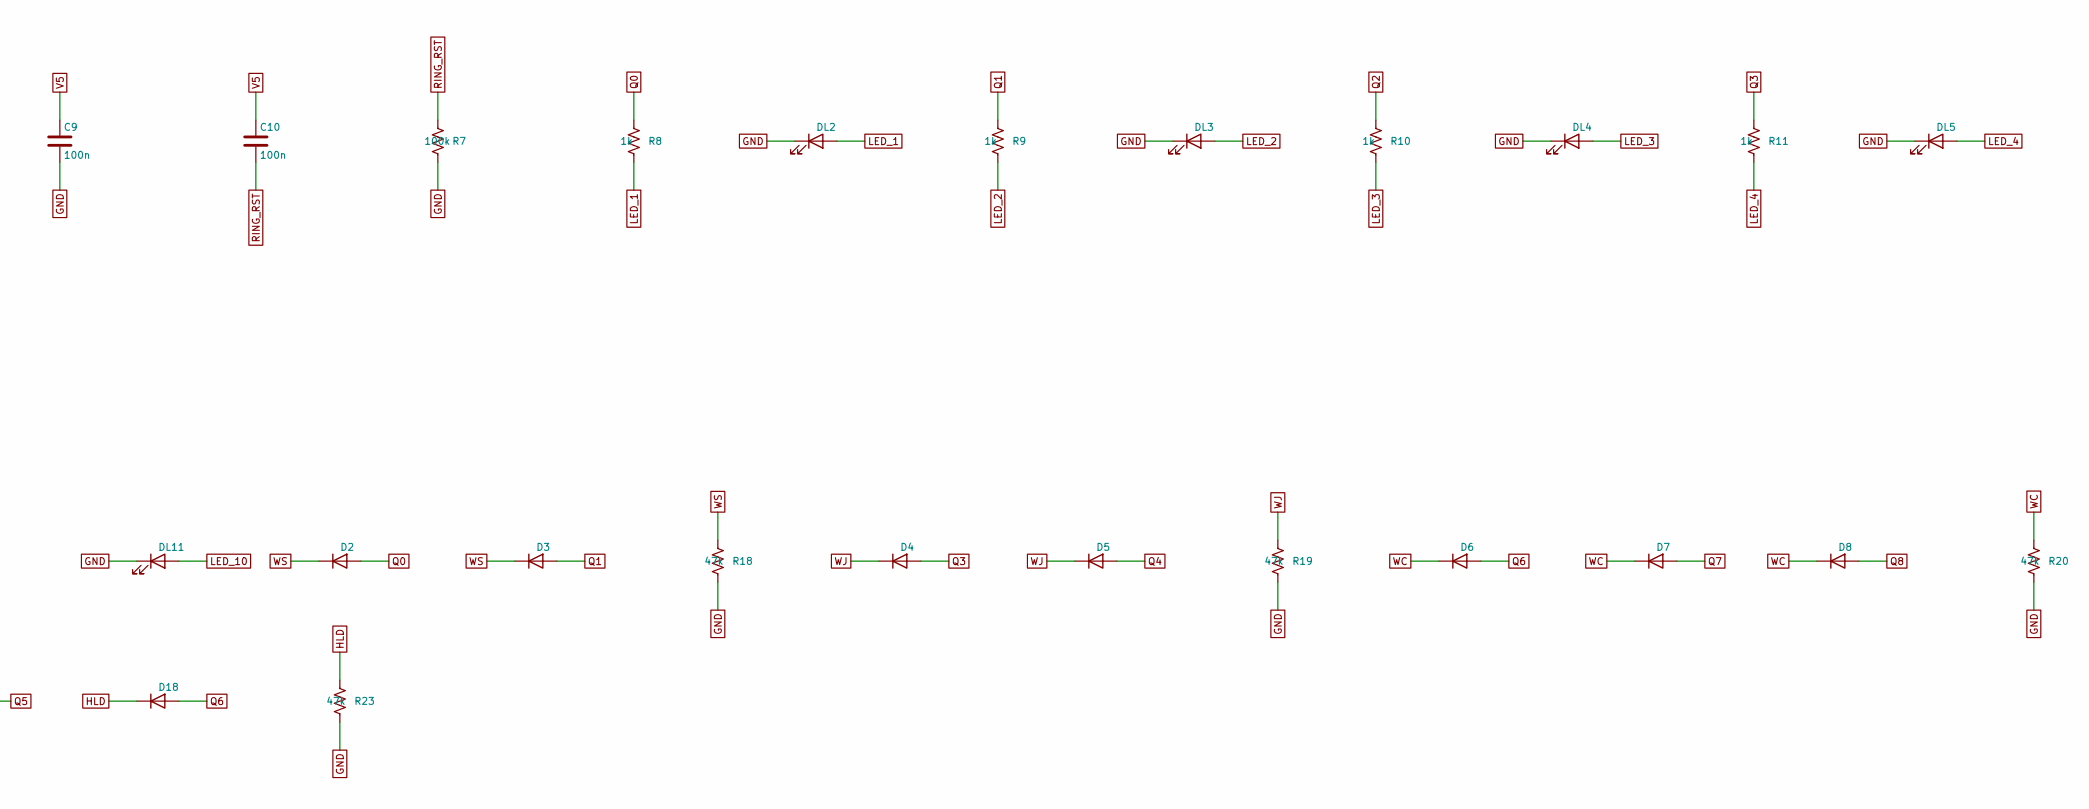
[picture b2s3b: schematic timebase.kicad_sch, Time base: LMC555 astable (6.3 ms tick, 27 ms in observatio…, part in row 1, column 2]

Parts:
C6: 22n C0G; C_0603_1608Metric
C7: 10n; C_0603_1608Metric
C8, C9, C10: 100n; C_0603_1608Metric
D2, D3, D4, D5, D6, D7, D8, D9, D10, D11, D12, D13, D14, D15, D16, D17, D18: 1N4148W; D_SOD-123
DL2, DL3, DL4, DL5, DL6, DL7, DL8, DL9, DL10, DL11: LED; LED_0603_1608Metric
R4: 10k; R_0603_1608Metric
R5: 680k; R_0603_1608Metric
R6: 150k; R_0603_1608Metric
R7: 100k; R_0603_1608Metric
R8, R9, R10, R11, R12, R13, R14, R15, R16, R17: 1k; R_0603_1608Metric
R18, R19, R20, R21, R22, R23: 47k; R_0603_1608Metric
RV1: 100k trim; Potentiometer_Bourns_3296W_Vertical
U1: LMC555; SOIC-8_3.9x4.9mm_P1.27mm
U2: 74HC4017; SOIC-16_3.9x9.9mm_P1.27mm

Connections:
CLK: U1.3 (OUT), U2.14 (CLK)
CTL: C7.1, U1.5 (CONT)
DIS: R4.2, R5.1, U1.7 (DISCH); also elsewhere on the board
GND: C6.2, C7.2, C8.2, C9.2, DL2.1 (K), DL3.1 (K), DL4.1 (K), DL5.1 (K), DL6.1 (K), DL7.1 (K), DL8.1 (K), DL9.1 (K), DL10.1 (K), DL11.1 (K), R7.2, R18.2, R19.2, R20.2, R21.2, R22.2, R23.2, U1.1 (GND), U2.8 (VSS); also elsewhere on the board
HKON: D11.1 (K), D12.1 (K), D13.1 (K), D14.1 (K), R22.1; also elsewhere on the board
HLD: D15.1 (K), D16.1 (K), D17.1 (K), D18.1 (K), R23.1; also elsewhere on the board
LED_1: DL2.2 (A), R8.2
LED_2: DL3.2 (A), R9.2
LED_3: DL4.2 (A), R10.2
LED_4: DL5.2 (A), R11.2
LED_5: DL6.2 (A), R12.2
LED_6: DL7.2 (A), R13.2
LED_7: DL8.2 (A), R14.2
LED_8: DL9.2 (A), R15.2
LED_9: DL10.2 (A), R16.2
LED_10: DL11.2 (A), R17.2
PARK: U2.13 (CKEN); also elsewhere on the board
Q0: D2.2 (A), R8.1, U2.3 (Q0)
Q1: D3.2 (A), R9.1, U2.2 (Q1)
Q2: R10.1, U2.4 (Q2)
Q3: D4.2 (A), D15.2 (A), R11.1, U2.7 (Q3)
Q4: D5.2 (A), D16.2 (A), R12.1, U2.10 (Q4)
Q5: D11.2 (A), D17.2 (A), R13.1, U2.1 (Q5)
Q6: D6.2 (A), D12.2 (A), D18.2 (A), R14.1, U2.5 (Q6); also elsewhere on the board
Q7: D7.2 (A), D9.2 (A), D13.2 (A), R15.1, U2.6 (Q7)
Q8: D8.2 (A), D10.2 (A), D14.2 (A), R16.1, U2.9 (Q8)
Q9: R17.1, U2.11 (Q9); also elsewhere on the board
RING_RST: C10.2, R7.1, U2.15 (Reset)
RM: R6.2, RV1.1
RSL: R5.2, R6.1; also elsewhere on the board
TH: C6.1, RV1.2, RV1.3, U1.2 (TRIG), U1.6 (THRES)
V5: C8.1, C9.1, C10.1, R4.1, U1.4 (~RST), U1.8 (VCC), U2.16 (VDD); also elsewhere on the board
WC: D6.1 (K), D7.1 (K), D8.1 (K), R20.1; also elsewhere on the board
WJ: D4.1 (K), D5.1 (K), R19.1; also elsewhere on the board
WK: D9.1 (K), D10.1 (K), R21.1; also elsewhere on the board
WS: D2.1 (K), D3.1 (K), R18.1; also elsewhere on the board
